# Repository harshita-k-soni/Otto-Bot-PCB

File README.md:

# Otto-Bot-PCB
Crafted a breakout board designed specifically for building the Otto Desk Bot, a popular project in the robotics community. This board incorporates essential components including the Arduino Nano, OLED display, HC-05 Bluetooth module, and servo motors. Created using KiCad 7, this breakout board streamlines the process of integrating these components, making it easier for hobbyists and enthusiasts to assemble the Otto Desk Bot.

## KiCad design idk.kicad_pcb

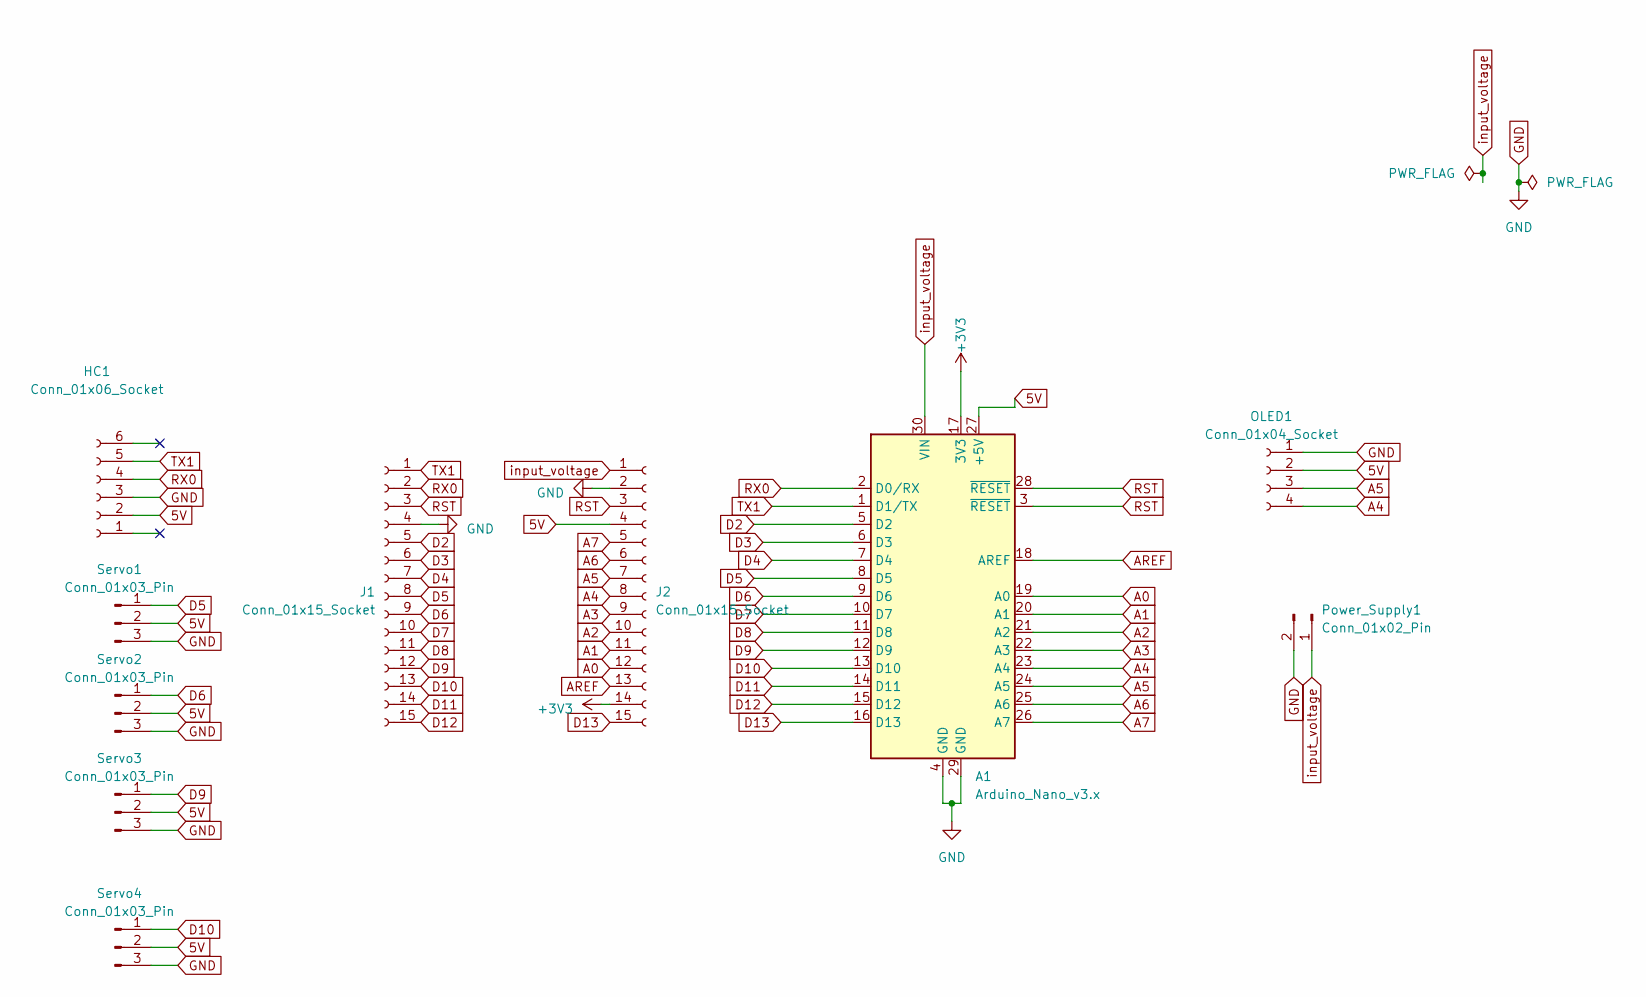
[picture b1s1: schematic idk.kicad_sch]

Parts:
A1: Arduino_Nano_v3.x; Arduino_Nano_WithMountingHoles
HC1: Conn_01x06_Socket; PinSocket_1x06_P2.54mm_Vertical
J1, J2: Conn_01x15_Socket; PinSocket_1x15_P2.54mm_Vertical
OLED1: Conn_01x04_Socket; PinSocket_1x04_P2.54mm_Vertical
Power_Supply1: Conn_01x02_Pin; PinSocket_1x02_P2.54mm_Vertical
Servo1, Servo2, Servo3, Servo4: Conn_01x03_Pin; PinHeader_1x03_P2.54mm_Vertical

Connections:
5V: A1.27 (+5V), HC1.2, J2.4, OLED1.2, Servo1.2, Servo2.2, Servo3.2, Servo4.2
+3V3: A1.17 (3V3), J2.14
A0: A1.19 (A0), J2.12
A1: A1.20 (A1), J2.11
A2: A1.21 (A2), J2.10
A3: A1.22 (A3), J2.9
A4: A1.23 (A4), J2.8, OLED1.4
A5: A1.24 (A5), J2.7, OLED1.3
A6: A1.25 (A6), J2.6
A7: A1.26 (A7), J2.5
AREF: A1.18 (AREF), J2.13
D2: A1.5 (D2), J1.5
D3: A1.6 (D3), J1.6
D4: A1.7 (D4), J1.7
D5: A1.8 (D5), J1.8, Servo1.1
D6: A1.9 (D6), J1.9, Servo2.1
D7: A1.10 (D7), J1.10
D8: A1.11 (D8), J1.11
D9: A1.12 (D9), J1.12, Servo3.1
D10: A1.13 (D10), J1.13, Servo4.1
D11: A1.14 (D11), J1.14
D12: A1.15 (D12), J1.15
D13: A1.16 (D13), J2.15
GND: A1.4 (GND), A1.29 (GND), HC1.3, J1.4, J2.2, OLED1.1, Power_Supply1.2, Servo1.3, Servo2.3, Servo3.3, Servo4.3
RST: A1.3 (~RESET), A1.28 (~RESET), J1.3, J2.3
RX0: A1.2 (D0/RX), HC1.4, J1.2
TX1: A1.1 (D1/TX), HC1.5, J1.1
input_voltage: A1.30 (VIN), J2.1, Power_Supply1.1

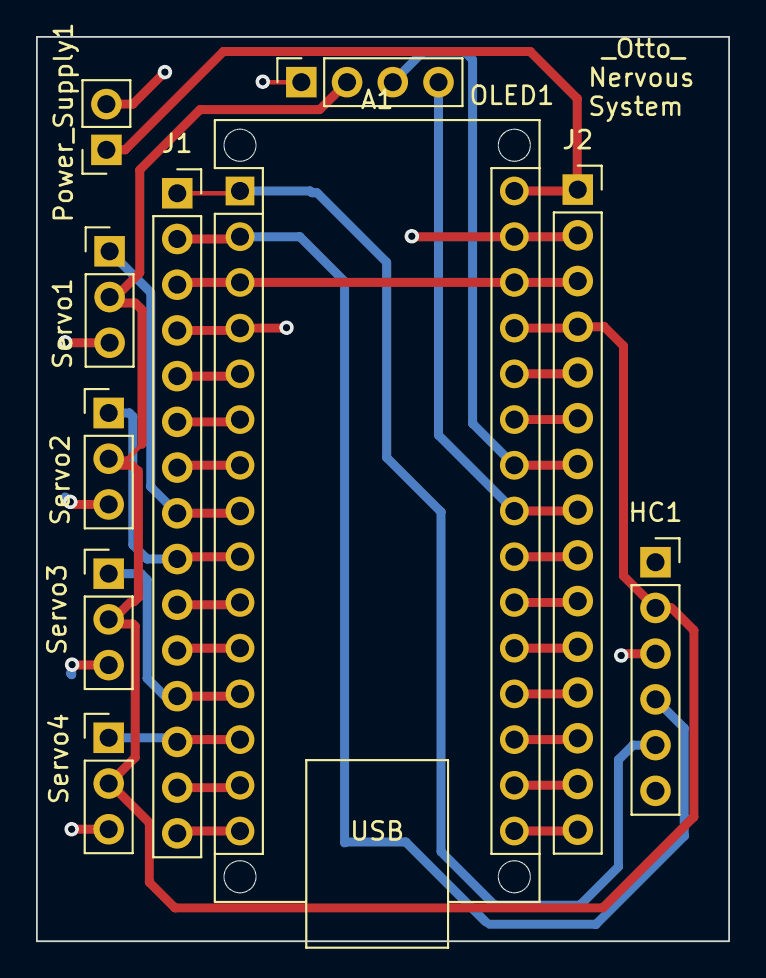
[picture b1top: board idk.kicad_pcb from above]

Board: 2 copper layers, 38.5 x 50.2 mm, 10 parts (0 on the bottom side), 28 nets.

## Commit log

2024-02-19 Connections of Breakout Board
2024-02-19 Layout of the pcb
    Contains the actual routing of the pcb i.e, how the actual connections will look like on pcb.
    Note: It is not the file which we send to the fabrication, after this we generate a gerber file and then send it to the pcb manufacturers.
